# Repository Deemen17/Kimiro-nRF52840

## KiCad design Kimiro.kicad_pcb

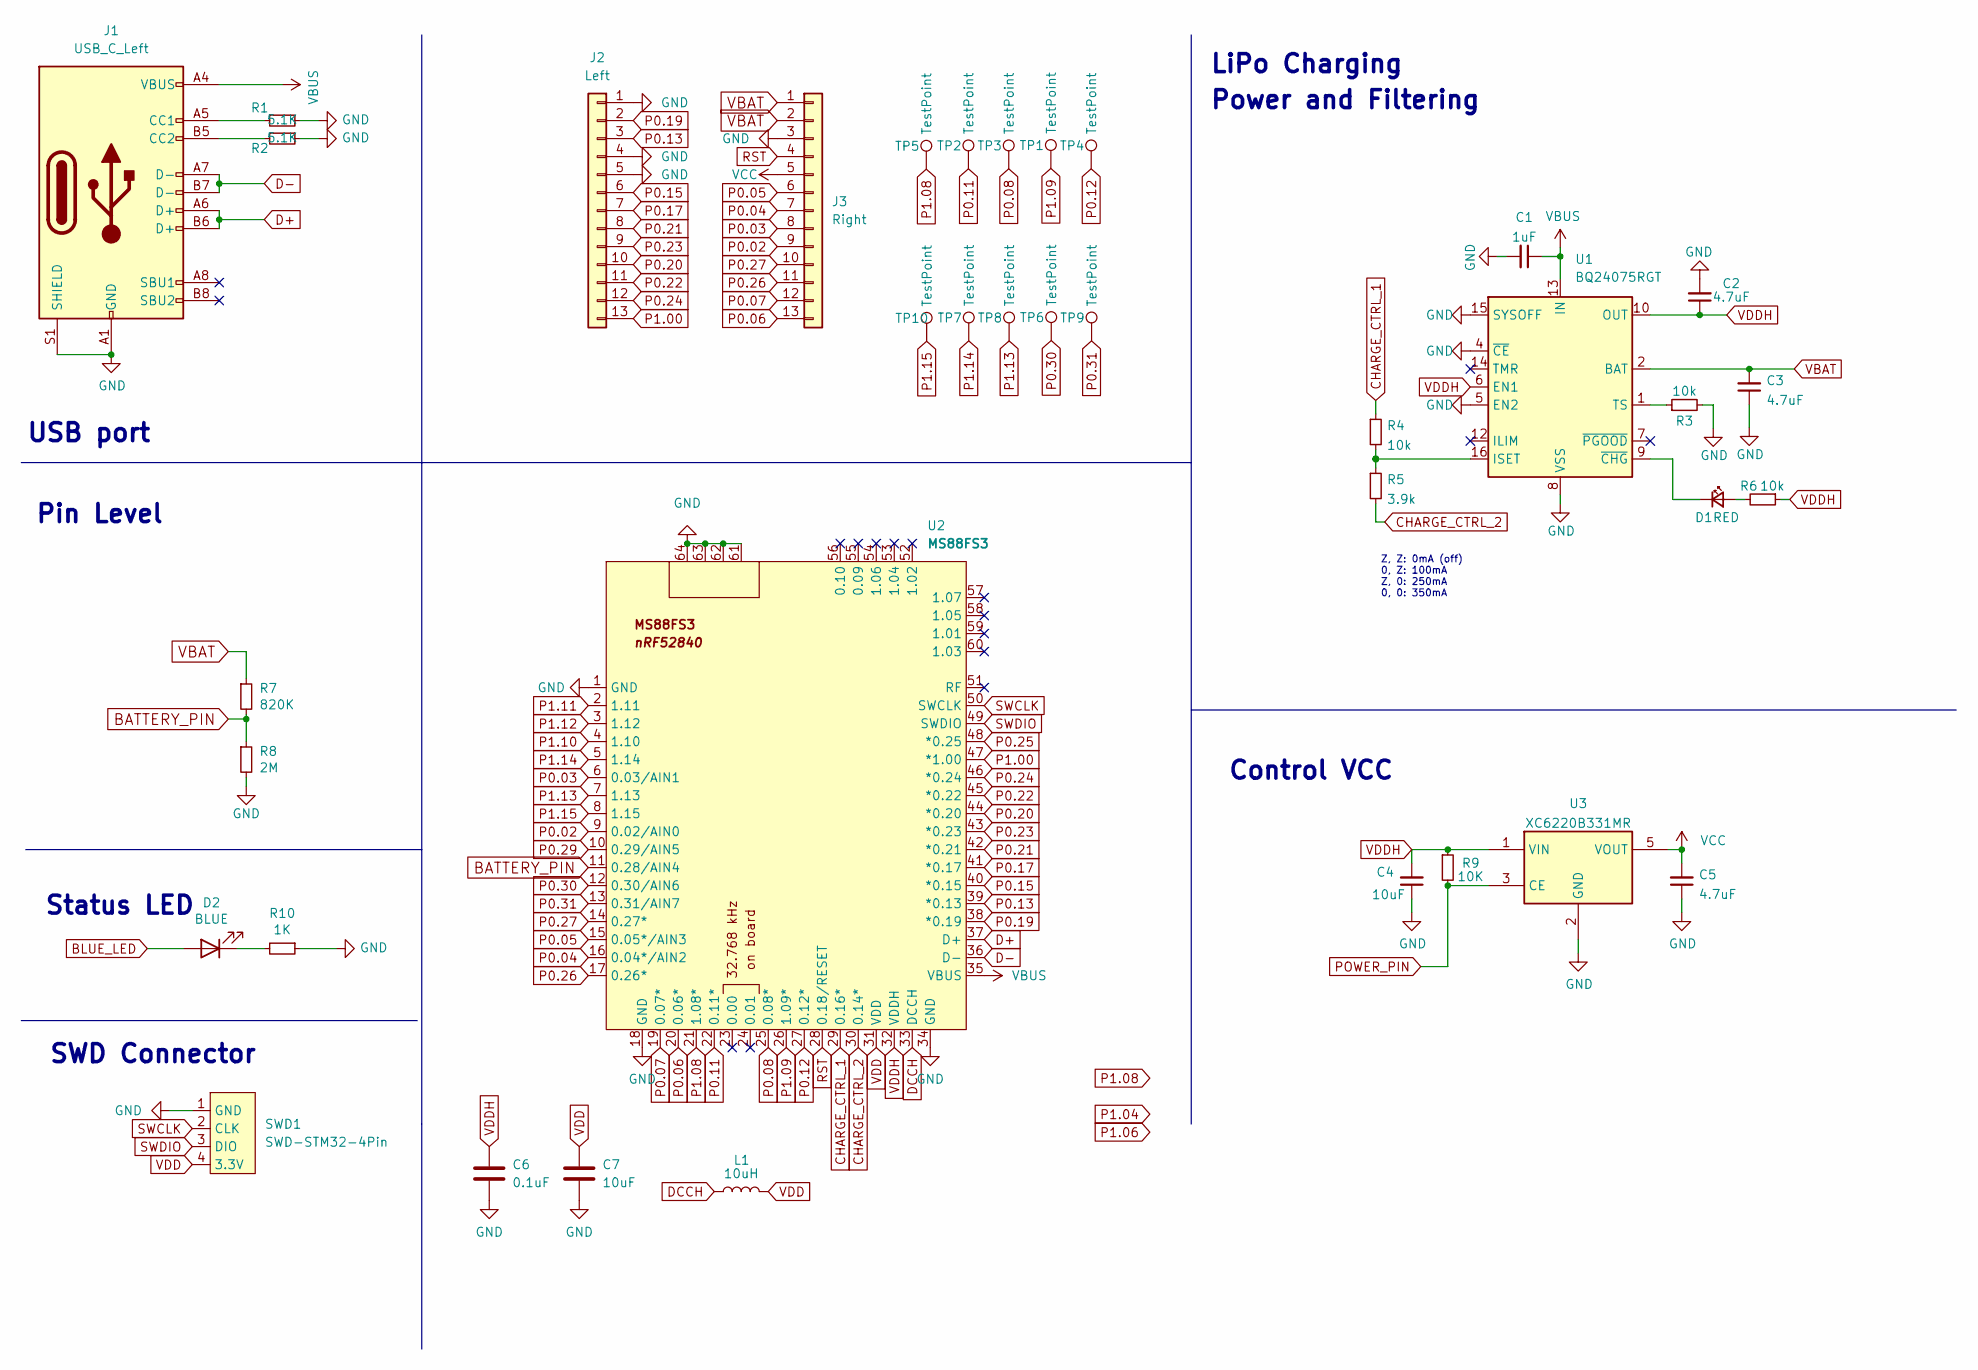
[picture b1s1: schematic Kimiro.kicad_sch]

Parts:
C1: 1uF; C_0402_1005Metric; Manufacturer Part CL05A105KO5NNNC; LCSC Part C52923
C2, C3, C5: 4.7uF; C_0402_1005Metric; Manufacturer Part CL05A475KP5NRNC; LCSC Part C368809
C4: 10uF; C_0402_1005Metric; Manufacturer Part CL10A106KP8NNNC; LCSC Part C19702
C6: 0.1uF; C_0402_1005Metric
C7: 10uF; C_0402_1005Metric
D1: RED; LED_0603_1608Metric; Manufacturer Part 19-217/S2C-AQ1R1B/3T; LCSC Part C160478
D2: BLUE; LED_0603_1608Metric; LCSC Part Number C375446
J1: USB_C_Left; USB-C_C168688
J2: Left; Conn_1x13_P2.54mm
J3: Right; Conn_1x13_P2.54mm
L1: 10uH; L_0603_1608Metric
R1, R2: 5.1K; C_0402_1005Metric
R3, R4, R6: 10k; R_0402_1005Metric; Manufacturer Part RC0402FR-0710KL; LCSC Part C60490
R5: 3.9k; R_0402_1005Metric; Manufacturer Part RC0402FR-073K9L; LCSC Part C131467
R7: 820K; R_0402_1005Metric
R8: 2M; R_0402_1005Metric
R9: 10K; R_0402_1005Metric; Manufacturer Part RC0402FR-0710KL; LCSC Part C60490
R10: 1K; R_0402_1005Metric; LCSC Part Number C21190
SWD1: SWD-STM32-4Pin; Conn_1x04_P2.54mm
TP1, TP2, TP3, TP4, TP5, TP6, TP7, TP8, TP9, TP10: TestPoint; TestPoint_Pad_1.5x1.5mm
U1: BQ24075RGT; VQFN-16-1EP_3x3mm_P0.5mm_EP1.6x1.6mm
U2: MS88FS3; MS88SF3-nRF52840
U3: XC6220B331MR; SOT-23-5; Manufacturer Part XC6220B331MR-G‎; Digikey 893-1133-1-ND‎

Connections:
BATTERY_PIN: R7.2, R8.1, U2.11 (0.28/AIN4)
BLUE_LED: D2.2 (A)
CHARGE_CTRL_1: R4.1, U2.29 (0.16*)
CHARGE_CTRL_2: R5.2, U2.30 (0.14*)
D+: J1.A6 (D+), J1.B6 (D+), U2.37 (D+)
D-: J1.A7 (D-), J1.B7 (D-), U2.36 (D-)
DCCH: L1.1, U2.33 (DCCH)
GND: C1.2, C2.2, C3.1, C4.1, C5.1, C6.2, C7.2, J1.A1 (GND), J1.A12 (GND), J1.B1 (GND), J1.B12 (GND), J1.S1 (SHIELD), J1.S2, J1.S3, J1.S4, J2.1, J2.4, J2.5, J3.3, R1.2, R2.1, R3.2, R8.2, R10.1, SWD1.1 (GND), U1.4 (~CE), U1.5 (EN2), U1.8 (VSS), U1.15 (SYSOFF), U1.17 (VSS), U2.1 (GND), U2.18 (GND), U2.34 (GND), U2.61, U2.62, U2.63, U2.64, U3.2 (GND)
unnamed: D1.1 (K), U1.9 (~CHG)
unnamed: D1.2 (A), R6.2
unnamed: D2.1 (K), R10.2
unnamed: J1.A5 (CC1), R1.1
unnamed: J1.B5 (CC2), R2.2
unnamed: R3.1, U1.1 (TS)
unnamed: R4.2, R5.1, U1.16 (ISET)
P0.02: J3.9, U2.9 (0.02/AIN0)
P0.03: J3.8, U2.6 (0.03/AIN1)
P0.04: J3.7, U2.16 (0.04*/AIN2)
P0.05: J3.6, U2.15 (0.05*/AIN3)
P0.06: J3.13, U2.20 (0.06*)
P0.07: J3.12, U2.19 (0.07*)
P0.08: TP3.1, U2.25 (0.08*)
P0.11: TP2.1, U2.22 (0.11*)
P0.12: TP4.1, U2.27 (0.12*)
P0.13: J2.3, U2.39 (*0.13)
P0.15: J2.6, U2.40 (*0.15)
P0.17: J2.7, U2.41 (*0.17)
P0.19: J2.2, U2.38 (*0.19)
P0.20: J2.10, U2.44 (*0.20)
P0.21: J2.8, U2.42 (*0.21)
P0.22: J2.11, U2.45 (*0.22)
P0.23: J2.9, U2.43 (*0.23)
P0.24: J2.12, U2.46 (*0.24)
P0.25: U2.48 (*0.25)
P0.26: J3.11, U2.17 (0.26*)
P0.27: J3.10, U2.14 (0.27*)
P0.29: U2.10 (0.29/AIN5)
P0.30: TP6.1, U2.12 (0.30/AIN6)
P0.31: TP9.1, U2.13 (0.31/AIN7)
P1.00: J2.13, U2.47 (*1.00)
P1.08: TP5.1, U2.21 (1.08*)
P1.09: TP1.1, U2.26 (1.09*)
P1.10: U2.4 (1.10)
P1.11: U2.2 (1.11)
P1.12: U2.3 (1.12)
P1.13: TP8.1, U2.7 (1.13)
P1.14: TP7.1, U2.5 (1.14)
P1.15: TP10.1, U2.8 (1.15)
POWER_PIN: R9.2, U3.3 (CE)
RST: J3.4, U2.28 (0.18/RESET)
SWCLK: SWD1.2 (CLK), U2.50 (SWCLK)
SWDIO: SWD1.3 (DIO), U2.49 (SWDIO)
VBAT: C3.2, J3.1, J3.2, R7.1, U1.2 (BAT), U1.3 (BAT)
VBUS: C1.1, J1.A4 (VBUS), J1.A9 (VBUS), J1.B4 (VBUS), J1.B9 (VBUS), U1.13 (IN), U2.35 (VBUS)
VCC: C5.2, J3.5, U3.5 (VOUT)
VDD: C7.1, L1.2, SWD1.4 (3.3V), U2.31 (VDD)
VDDH: C2.1, C4.2, C6.1, R6.1, R9.1, U1.6 (EN1), U1.10 (OUT), U1.11 (OUT), U2.32 (VDDH), U3.1 (VIN)

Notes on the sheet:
Power and Filtering
Status LED
LiPo Charging
Control VCC
Pin Level
SWD Connector
Z, Z: 0mA (off) 0, Z: 100mA Z, 0: 250mA 0, 0: 350mA
USB port

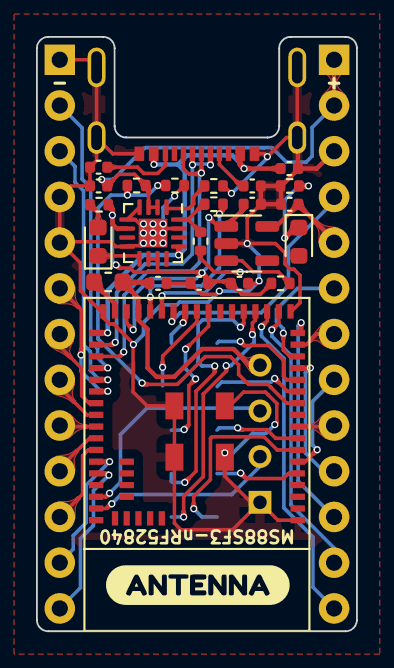
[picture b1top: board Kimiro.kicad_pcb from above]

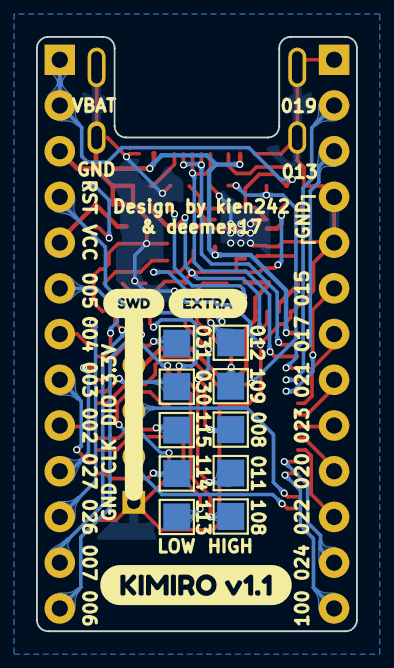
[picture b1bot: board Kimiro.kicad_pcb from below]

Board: 2 copper layers, 17.8 x 33.0 mm, 41 parts (13 on the bottom side), 51 nets.

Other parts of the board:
kibuzzard-62308F3A: G***; kibuzzard-62308F3A
kibuzzard-62308F5E: G***; kibuzzard-62308F5E
kibuzzard-623091BE: G***; kibuzzard-623091BE
kibuzzard-6230908B: G***; kibuzzard-6230908B

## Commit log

2022-03-15 Kicad PCB design ver 1.1
2022-03-15 Fix VBUS trace nears USB edge-cut
2022-03-15 Remove some needless via
2022-03-16 Check again and add note slikscreen for extra pins
